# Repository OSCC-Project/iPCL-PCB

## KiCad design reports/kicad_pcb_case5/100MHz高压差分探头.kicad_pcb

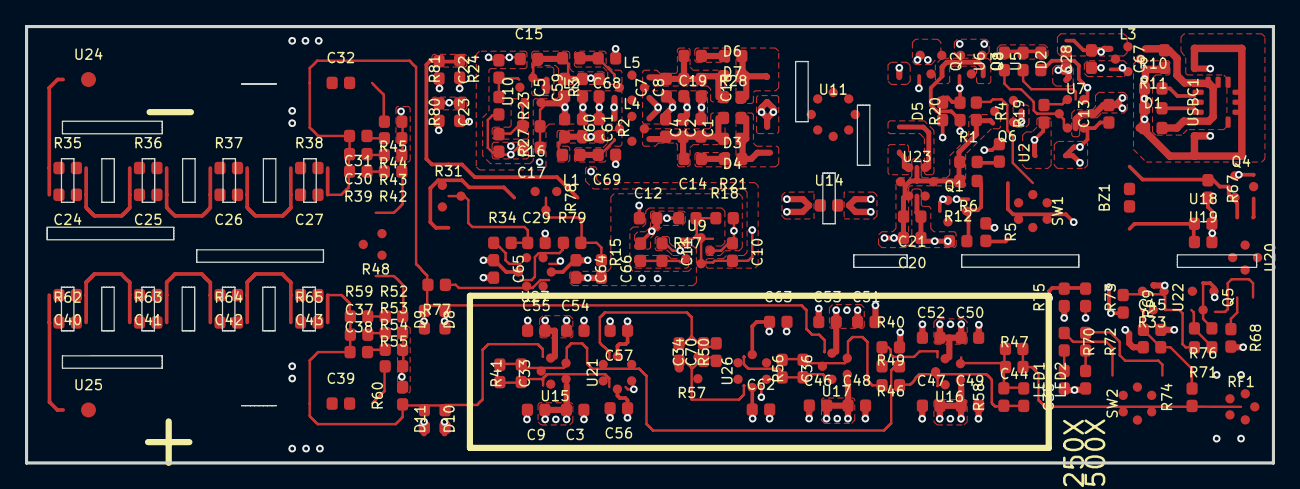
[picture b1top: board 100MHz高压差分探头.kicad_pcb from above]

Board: 4 copper layers, 100.0 x 35.0 mm, 185 parts (0 on the bottom side), 91 nets.

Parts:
BZ1: 3f1529bbaa4c4125a10b70c2df94fc11
C1, C2, C3, C4, C5, C7, C8, C9, C10, C11, C12, C13, C14, C15, C16, C17, C18, C19, C20, C21, C22, C23, C28, C29, C30, C31, C33, C35, C36, C37, C38, C44, C45, C46, C47, C48, C49, C50, C51, C52, C53, C54, C55, C56, C57, C59, C60, C61, C62, C63, C64, C65, C66, C67, C68, C69: 01a79b0e39434d2ea8de62503f4b7cf0
C24, C25, C26, C27, C40, C41, C42, C43: 50b6f6c4261345bcae1f204b32f03376
C32, C39: 0bbfdf4e88d143f6bbe0c44ba3fab90c
C34, C70: b083607f37af4680b9e4592262e65319
D1, D3, D4, D5, D6, D7, D8, D9, D10, D11: 2221e8d1e2a34b8f89d77a5d79f2ca10
D2: 2d40e6deeb29450e9d1a4a76727988d5
L1, L2: f3d986930d2e4bc98811ac8ef379dce3
L3, L4, L5: a09d160eb8b243d5bb85ea6fb6939f0f
LED1: 65745c81ed8e4f3d8e50d31c896d1acd
LED2: 897dac56033e486aafb175e0d8b9fbf8
Q1, Q2, Q3, Q5, Q6: f399c43c22204b4fb713e57500bec75f
Q4: 2af9f62ae7c849819938fc866dd93b51
R1, R2, R3, R4, R5, R6, R10, R11, R12, R15, R17, R18, R19, R20, R21, R23, R24, R27, R28, R33, R34, R39, R40, R41, R42, R43, R44, R45, R46, R47, R49, R52, R53, R54, R55, R56, R58, R59, R60, R67, R68, R69, R70, R71, R72, R73, R74, R75, R76, R77, R79, R80, R81: 345df099f6c344ecb03f6331ff1faf22
R31, R48, R57, R78: 507339a48b6e4fd2b68fda0a46e27918
R35, R36, R37, R38, R62, R63, R64, R65: 50b6f6c4261345bcae1f204b32f03376
R50: b083607f37af4680b9e4592262e65319
RF1: 1ec777233d6c4149af6d04cb8e51bfe0
SW1, SW2: 48ba2fcf414c4ed1a85436e39ba2de45
U2, U6, U8: 7f88689ddd524e799a2641e85c3efaab
U5, U18, U19: 345df099f6c344ecb03f6331ff1faf22
U7, U23: 3b6e914cb86f4d04bf420dafbc51a538
U9: c412defa74a04dd7acaf0683044d5107
U10: 3a5982d0234d420ea4a672c9ef07185e
U11: a63def889ecb4197ab4f0e3660f255c6
U14: 1ff305d16cc04ffa85117006eafe7e4e
U15, U16, U17: 78df07149524430e9275017333e781e3
U20: 9a9a9ba2542742fcbc0be96d8fc2a154
U21, U26, U27: 34bb1eb335204bddbf3cbc7fe83f455e
U22: f399c43c22204b4fb713e57500bec75f
U24, U25: 0ff93004c7c14642a7edf0b7216f2991
USBC1: d71d1ea865754169be761115f6d42a03

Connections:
50X_BIAS_IN: R79.1, U27.3
500X_BIAS_IN: R34.1, U27.1
$1N9: R10.2, USBC1.B5
$1N10: R11.2, USBC1.A5
$1N17: D6.2, D7.2, R28.1, U11.5
$1N18: C14.1, R21.2
$1N19: C19.1, R28.2
$1N29: R19.2, U7.6
$1N31: U6.1, U7.1
$1N32: U7.5, U8.1
$1N34: U5.2, U6.2, U8.2
$1N35: Q2.2, Q3.2, R20.1
$1N37: D3.1, D4.1, R21.1, U11.8
$1N38: Q1.3, U2.1
$1N39: Q1.1, R6.1, R12.2
$1N42: R1.2, U2.2
$1N44: D5.2, Q2.1, Q3.1, R20.2, SW1.2
$1N50: U11.2, U23.4
$1N51: U11.1, U23.6
$1N70: C11.2, R15.1, U9.5
$1N80: C16.2, R27.1, U10.5
$1N84: R17.1, R18.1, U9.4
$1N85: R23.1, R24.1, U10.4
$1N87: R5.2, SW1.3
$1N88: Q6.1, R4.1, SW1.5
$1N8838: C69.2, L1.1, L4.4
$1N8925: C68.2, L2.1, L5.1
$2N9: C35.1, C44.2, R47.1, R58.2, U16.1
$2N10: C36.1, R49.1, R56.2, U17.1
$2N11: C33.1, R41.2, R46.1, U15.1
$2N13: R40.1, R46.2, U16.3
$2N15: C35.2, R49.2, R58.1, U16.4
$2N40: C32.2, R45.2
$2N44: C24.2, R35.1, U24.1
$2N45: C40.2, R62.1, U25.1
$2N46: R52.1, R59.2
$2N47: R48.1, R52.2
$2N48: C40.1, C41.2, R62.2, R63.1
$2N50: C41.1, C42.2, R63.2, R64.1
$2N51: C42.1, C43.2, R64.2, R65.1
$2N55: R42.1, R48.3
$2N56: R39.1, R42.2
$2N57: C26.1, C27.2, R37.2, R38.1
$2N58: C25.1, C26.2, R36.2, R37.1
$2N60: C24.1, C25.2, R35.2, R36.1
$2N70: R73.2, SW2.6
$2N71: R70.1, SW2.1
$2N72: R72.1, SW2.3
$2N74: LED1.2, R70.2
$2N75: LED2.2, R72.2
$2N78: C45.1, R33.2, R74.2, U22.1
$2N83: R69.1, R71.2, U22.2
$2N86: R68.1, U20.1
$2N88: Q5.1, R71.1, R76.2
$2N90: Q4.1, U20.3
$2N92: BZ1.1, U18.1, U19.1
$2N93: BZ1.2, Q4.3, R67.1, U20.4
$2N95: C31.1, R44.2
$2N96: C37.2, R53.1
$2N97: C30.1, R43.2
$2N98: C38.2, R54.1
$2N127: C39.2, R55.1
$2N12584: Q5.2, U20.2
$2N25458: C29.1, R31.2, R34.2
$2N25616: C66.1, R78.2, R79.2
+2.5V: C3.2, C9.1, C12.2, C46.2, C47.2, C48.1, C49.1, C56.1, C62.1, C64.1, D8.2, D10.2, R15.2, R17.2, R80.1, SW2.4, SW2.5, U15.5, U16.5, U17.5, U21.5, U26.5, U27.5
+4.5V: C10.2, C60.2, C61.2, L1.2, R2.2, R68.2, R69.2, SW2.2, U9.1, U9.3
+5V: C20.2, C21.2, D2.1, Q3.3, Q6.2, R1.1, R4.2, R6.2, R67.2, SW1.6, U18.2, U19.2, U23.1, U23.5
+VCC: C1.2, C2.2, C4.1, C14.2, D3.2, D4.2, L4.3
-2.5V: C17.2, C50.1, C51.1, C52.2, C53.2, C54.1, C55.2, C57.1, C63.1, C65.1, D9.1, D11.1, R23.2, R27.2, R75.1, R81.1, U15.2, U16.2, U17.2, U21.2, U26.2, U27.2
-4.5V: C5.2, C15.2, C59.2, L2.2, LED1.1, LED2.1, Q5.3, R3.2, R76.1, U10.2, U10.3
-VCC: C7.2, C8.2, C18.1, C19.2, D6.1, D7.1, L5.2
BAT+: C13.1, Q2.3, U7.3
BAT_CHRG: Q6.3, U5.1, U7.4
BIAS_OUT: R77.1, U27.4
EGND: C67.1, D1.1, L3.3, R10.1, R11.1, USBC1.1, USBC1.2, USBC1.3, USBC1.4, USBC1.A12, USBC1.B12
GND: C3.1, C5.1, C9.2, C10.1, C11.1, C12.1, C15.1, C16.1, C17.1, C22.2, C23.2, C29.2, C45.2, C46.1, C47.1, C48.2, C49.2, C50.2, C51.2, C52.1, C53.1, C54.2, C55.1, C56.2, C57.2, C59.1, C60.1, C61.1, C62.2, C63.2, C64.2, C65.2, C66.2, C68.1, C69.1, L4.1, L5.4, R2.1, R3.1, R18.2, R24.2, R33.1, R40.2, R43.1, R44.1, R45.1, R48.2, R53.2, R54.2, R55.2, R60.2, RF1.1, RF1.2, RF1.3, RF1.4, U9.2, U10.1, U22.3
HV_IN+: C37.1, C38.1, C39.1, C43.1, D10.1, D11.2, R59.1, R60.1, R65.2, U15.3
HV_IN-: C27.1, C30.2, C31.2, C32.1, D8.1, D9.2, R38.2, R39.2, R77.2, U17.3
PGND: C13.2, C20.1, C21.1, C28.1, L3.4, Q1.2, Q4.2, R5.1, R12.1, R19.1, SW1.4, U7.2, U11.4, U14.2, U23.2
POWER_IN: C67.2, D1.2, L3.2, USBC1.A9, USBC1.B9
SET_EN: R73.1, R75.2, U21.6, U26.6, U27.6
SGND: C1.1, C2.1, C4.2, C7.1, C8.1, C18.2, L4.2, L5.3, U11.6, U11.7, U14.1
SIGNAL_A: C33.2, R41.1, U15.4, U21.4
SIGNAL_B: C34.2, C70.2, R50.1, R57.3, U21.3
SIGNAL_C: C34.1, C70.1, R50.2, R57.1, R57.2, U26.4
SIGNAL_D: C36.2, R56.1, U17.4, U26.3
SIGNAL_OUT: C44.1, R47.2, R74.1, RF1.5
VBUS: C28.2, D2.2, D5.1, L3.1
VCC_BIAS: C23.1, R31.3, R78.3, R80.2
VSS_BIAS: C22.1, R31.1, R78.1, R81.2

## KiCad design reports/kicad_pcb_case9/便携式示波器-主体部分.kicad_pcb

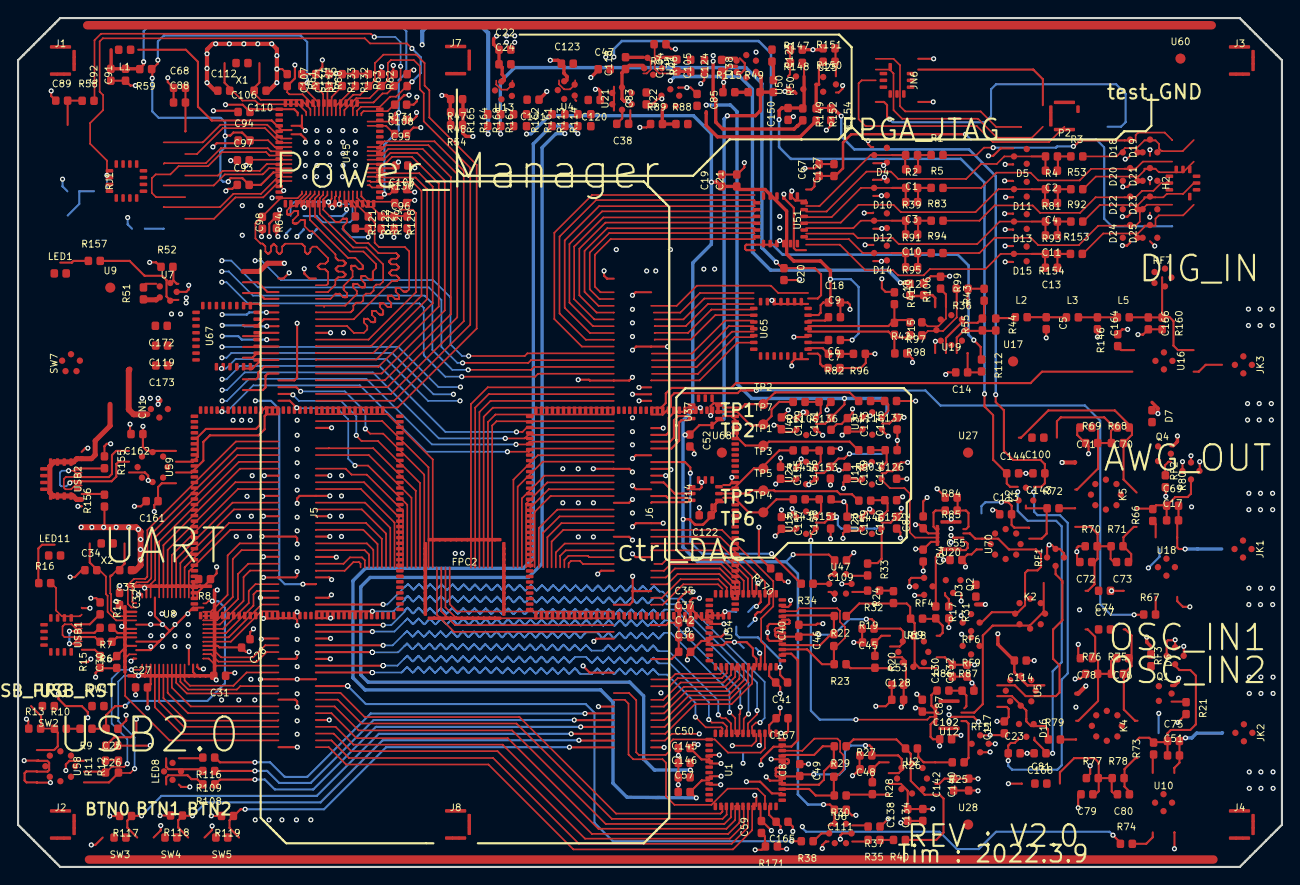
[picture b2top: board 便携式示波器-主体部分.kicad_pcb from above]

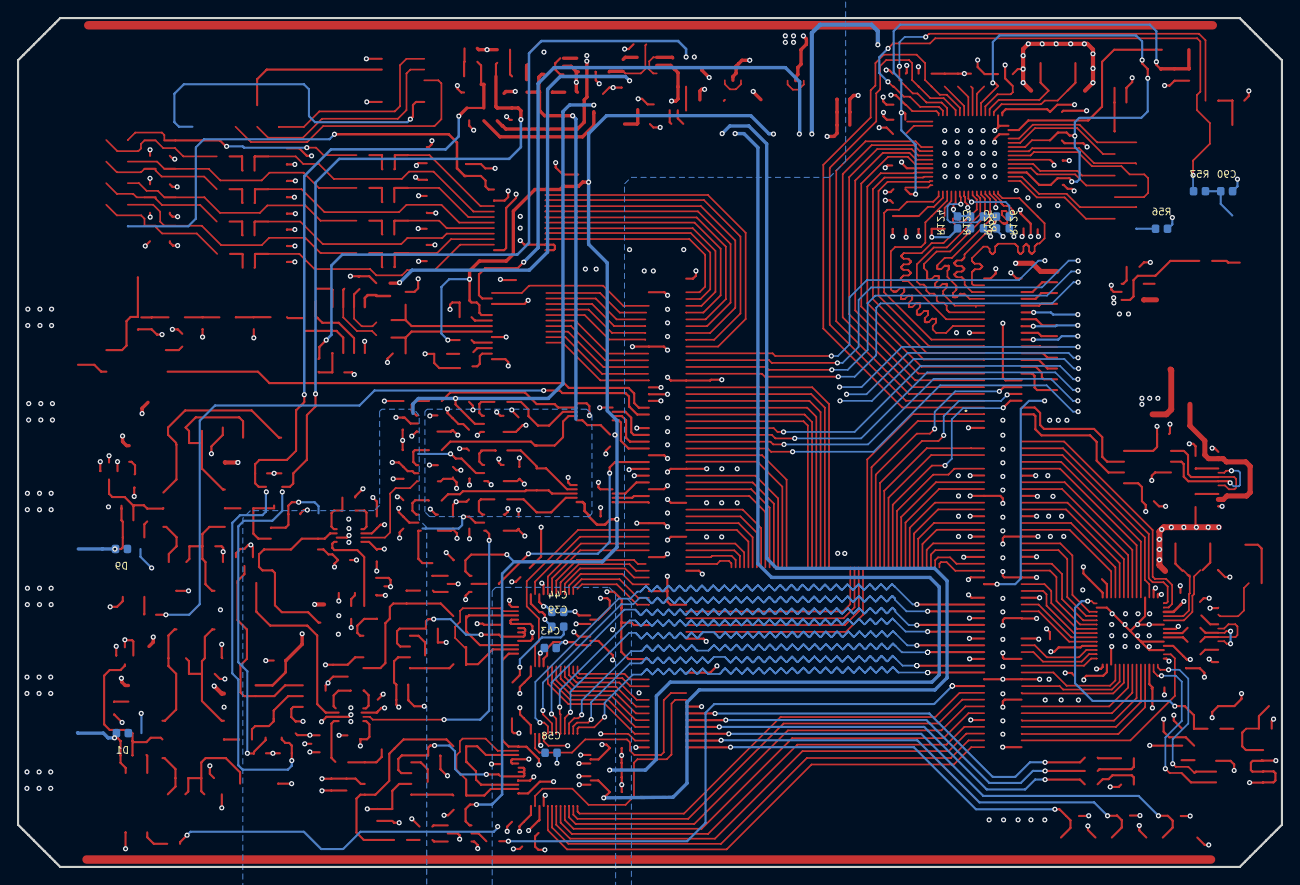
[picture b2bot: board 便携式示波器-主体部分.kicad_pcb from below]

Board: 4 copper layers, 148.8 x 100.0 mm, 424 parts (14 on the bottom side), 396 nets.

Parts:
C1, C2, C3, C4, C5, C6, C7, C8, C9, C10, C11, C12, C13, C14, C16, C17, C18, C19, C20, C21, C22, C23, C24, C25, C26, C27, C28, C30, C31, C32, C35, C36, C37, C38, C39, C40, C41, C42, C43, C44, C45, C47, C48, C50, C51, C52, C53, C55, C57, C58, C59, C67, C68, C69, C75, C82, C83, C84, C85, C87, C88, C89, C90, C91, C92, C93, C94, C95, C96, C97, C98, C102, C103, C104, C105, C106, C107, C108, C109, C111, C113, C114, C117, C118, C120, C121, C122, C123, C124, C126, C127, C128, C129, C130, C131, C132, C133, C134, C135, C136, C137, C138, C139, C140, C141, C142, C143, C144, C145, C146, C150, C151, C152, C153, C154, C155, C156, C157, C158, C159, C160, C161, C162, C164, C165, C166, C167, C168, C171: 07a3b3d25cb24a23b41b29c7c43f76a4
C15, C33, C34, C46, C49, C70, C71, C72, C73, C76, C78, C79, C80, C110, C112, C125: ecf74e3ff335461599c94ce8e76dec14
C74, C77, C81, C100: 6fe1afaffdd746fdafbe654c8791fdbb
C119: e953
C172: e643
C173: e975
CN1: 97ec1ec1f0bd4617b79c42a0c47e9ab8
D1, D9: 5c734f664c17495bb14b7ecc2dc1b01d
D2, D4, D5, D10, D11, D12, D13, D14, D15, D16: 7077287a35204f9fafd72688a0c6c785
D3, D6, D7: a427f604374a450b87681949da315927
D18, D19, D20, D21, D22, D23, D24, D25: ba35f145f3334095baaa2c5d5d7ab9c4
FPC2: acd62fa7532c46e08cf669b9fb3d13ec
H2: e31
J1, J2, J3, J4, J7, J8: 3e270af6f27d4b5baf20436f71ab87c1
J5, J6: 836487c508f5438db19a04d639868192
JK1, JK2, JK3: d6ee2ffcc263406887e9d63c7b0519c9
JN6: 634f5b4bbd774284bf12773d4cedab9f
K2, K4, K5: eac199bb981b499388a4d5b0c93f63eb
L1: cd119f9e95084eb78cad3b7cd4ac4ea6
L2, L3, L5: 5d95bff7b0ab48bfa5dc7e220d271b5c
LED1, LED11: 40f9432dd09647dfa891c462f023b0b0
LED8: e8caabb99a05482f87a41ff9bf5e5609
P2: 8c9b220d407a4bc496bdc03fba551d8c
Q1, Q2, Q4: 3287ea164c0a4816a855ac08f4e68882
R1, R2, R3, R4, R5, R6, R7, R8, R9, R10, R11, R12, R13, R14, R15, R16, R17, R18, R19, R20, R21, R22, R23, R24, R25, R26, R27, R28, R29, R30, R31, R32, R33, R34, R35, R36, R37, R38, R39, R40, R41, R42, R43, R44, R45, R46, R47, R48, R49, R50, R51, R52, R53, R54, R55, R56, R57, R58, R59, R60, R61, R62, R63, R64, R65, R66, R67, R68, R69, R70, R71, R72, R73, R74, R75, R76, R77, R78, R79, R80, R81, R82, R83, R84, R85, R86, R87, R88, R89, R90, R91, R92, R93, R94, R95, R96, R97, R98, R99, R106, R108, R109, R110, R111, R112, R113, R114, R115, R116, R117, R118, R119, R121, R122, R123, R124, R125, R126, R127, R128, R129, R130, R131, R132, R133, R134, R135, R143, R144, R145, R146, R147, R148, R149, R150, R151, R152, R153, R154, R155, R156, R157, R160, R161, R162, R164, R165, R167, R168, R170, R171: 43e5336c61b34dc782468a16d014e54d
RF1: e240
RF2: e2175
RF3: e25
RF4, RF5, RF6, RF9: 4e1d505314b3485a805716e4f50938d0
RF7: e4576
RJ1: 3276e94015d243a8b1987b283792c934
SW1, SW2, SW3, SW4, SW5: 7bb28a98aeac42d1ad801580e2fd9f70
SW7: e199
TP1, TP2, TP3, TP4, TP5, TP7: a4d664abb7a84b85a721b0f8f4caac91
U1, U54: 73b97067b09c48fdada0ea156bb47d30
U2: e231
U3, U11, U15, U23, U24, U38, U40: e9e4340cd3bd4d00a98771ccbc2147d9
U4, U13, U31: a5e6817750744227afed6be8097af0e7
U5, U58, U70: cc666a3ed81142bf901b0a0a8eae77fe
U6, U21, U47: 3046c1046c0c445eaf4abd679cb86288
U7, U22: e6e3948347364938bef4679a6c12bf30
U8: 053d832a12d44255a6c20dd47eb12ddf
U9: e4138
U10, U16, U18: 8c8b562b2c5a4e9f8b0b666146522526
U12, U20: d6e84d3e079e4e6d93029185448293be
U14, U37: 0e9d827b01c2473595ccff7f821a0fa7
U17: e123
U19: 09ce974493c54d8f8ba4eda961c351e3
U25, U50: 3287ea164c0a4816a855ac08f4e68882
U27, U28, U68: 2a0be85b264c426c9105224b5d9be198
U45: e3aaf21cb8f74bf5b3ffddae42e3b778
U51: e09dcdb7932c4e7fbdbbbb8b6cb2ff6e
U59: 44120597447e46d79e3593f8a78a64d1
U60: e2722
U65: e46
U67: e4557
U69: e214
USB1, USB2: b67455ad1fe74fee852a4e157a78bad8
X1, X2: 970fb1cc16ad4744a5ddbbdc55b3fc45

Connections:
1V8_VREF: R49.2, R50.2, U3.4, U11.4, U14.5, U15.4, U23.4, U24.4, U37.5, U38.1, U40.4
$2N3316: R8.2, U8.44
$2N3328: R10.1, R13.2, SW2.2, U58.1
$2N22466: LED11.1, R16.1
$4N2102: R51.2, U7.4
$4N2693: R52.2, U7.3
$4N30038: C38.2, U21.5
$4N30093: C38.1, U21.6
$4N32180: R88.1, R89.2, U22.4
$4N58970: C104.1, R45.2, R46.1, U31.4
$4N102963: R147.1, R148.2, U50.2
$4N105094: R150.1, R151.2, U25.2
$4N131424: C119.1, C172.1, C173.1, CN1.1, R51.1, SW7.2, U7.5
$6N577: C17.2, C69.2, D9.1, JK1.1, U18.3
$6N625: R66.1, U18.4
$6N717: R67.2, U18.1
$6N1817: C70.1, C100.2, K5.7, R68.2
$6N1853: C70.2, C71.1, C100.1, K5.2, R68.1, R69.2
$6N2746: C72.1, C73.2, C74.2, K5.4, R70.2, R71.1
$6N2880: C73.1, K5.5, R71.2
$6N3162: K5.3, R72.2
$6N3340: D2.3, R72.1, U70.3
$6N5199: C76.1, C77.2, K4.7, R75.2
$6N5200: C51.1, C75.1, K4.6, R73.2, RF3.1
$6N5202: C76.2, C77.1, C78.1, K4.2, R75.1, R76.2
$6N5203: C79.1, C80.2, C81.2, K4.4, R77.2, R78.1
$6N5204: C80.1, K4.5, R78.2
$6N5206: K4.3, R79.2
$6N5207: D16.3, R79.1, U5.3
$6N11215: R73.1, U10.4
$6N11216: C51.2, C75.2, D1.1, JK2.1, U10.3
$6N11218: R74.2, U10.1
$6N42224: Q4.1, R80.1
$6N42735: Q1.1, R21.1
$6N46533: C17.1, C69.1, K5.6, R66.2, RF2.1
$9N6643: LED1.1, R157.1
$9N15851: LED8.2, R108.2
$9N15883: LED8.4, R116.2
$9N16326: LED8.3, R109.2
$11N594: R84.1, U20.5
$11N596: R84.2, R85.1, U20.4
$11N600: R86.1, U12.5
$11N602: R86.2, R87.1, U12.4
$11N609: K2.6, RF9.1, U12.3
$11N2263: R17.1, RF4.1, U20.1
$11N2434: R25.1, RF5.1, U12.1
$11N15082: R32.2, U47.1
$11N15190: R33.2, U47.3
$11N21228: R17.2, R18.1, U69.8
$11N21637: R18.2, R22.1, R24.1, U69.5
$11N21987: R20.2, R23.1, U69.4
$11N32769: R28.2, R30.1, U2.4
$11N32770: R25.2, R26.1, U2.8
$11N32771: R26.2, R29.1, R40.1, U2.5
$11N32776: R27.2, R28.1, U2.1
$11N34575: R19.2, R20.1, U69.1
$11N44064: R34.1, U47.5
$11N45056: R35.2, U6.1
$11N45057: R37.2, U6.3
$11N45063: R38.1, U6.5
$11N62502: Q2.1, R31.1
$13N19030: JK3.1, U16.3
$13N22280: C164.1, L3.2, L5.1
$13N50350: R97.1, R99.2, U19.3
$13N50358: R36.2, R98.1, U19.2
$13N50720: R36.1, R43.2, U19.1
$13N50935: C15.1, R41.2, R97.2, U65.22
$13N50945: C15.2, R42.1, R98.2, U65.21
$13N51622: C5.1, L2.2, L3.1
$13N51745: R43.1, R55.2, U19.6
$13N52041: R44.2, R55.1, U19.7
$13N52059: L2.1, R44.1
$13N52787: C6.1, U65.17
$13N53261: R82.2, U65.18
$13N53282: R82.1, R96.2
$13N53522: C7.2, U65.19
$13N53699: C9.1, U65.23
$13N53994: R146.1, U16.1
$13N54030: C166.1, L5.2, R160.1, RF7.5, U16.4
$14N2427: C68.2, C88.2, RJ1.P1
$14N2610: R56.2, RJ1.P10
$14N2784: C89.2, R58.1, RJ1.11
$14N2791: C90.2, R57.1, RJ1.13
$14N17231: R134.1, U45.56
$14N17305: R135.2, U45.58
$14N17416: C110.2, U45.61, X1.1
$14N17453: C112.2, U45.62, X1.2
$15N1230: C136.2, R110.1, U40.3
$15N1237: C137.2, R111.1, U3.3
$15N1251: C126.2, R90.1, U11.3
$15N4262: C151.2, R143.1, U15.3
$15N4269: C152.2, R144.1, U23.3
$15N4283: C153.2, R145.1, U24.3
$15N8686: C125.2, R50.1
$15N15216: R49.1, R115.2
$16N832: C1.1, R1.1, R2.1
$16N1245: C2.1, R3.1, R4.1
$16N1889: C3.1, R5.1, R39.1
$16N2210: C4.1, R53.1, R81.1
$16N3886: C10.1, R83.1, R91.1
$16N3891: C11.1, R92.1, R93.1
$16N3896: C12.1, R94.1, R95.1
$16N3901: C13.1, R153.1, R154.1
+VA: C53.2, C55.2, C84.1, C102.1, C104.2, C105.2, C114.2, C124.2, C128.2, C129.2, C133.2, C134.2, C138.2, C139.2, C155.2, C157.2, C159.2, D3.1, D6.1, D7.1, K2.1, K4.1, K5.1, R46.2, R146.2, R149.2, U2.3, U3.6, U5.7, U11.6, U12.8, U15.6, U20.8, U23.6, U24.6, U31.5, U38.4, U38.6, U40.6, U69.3, U70.7
-VA: C82.1, C85.2, C87.2, C113.2, C117.2, C130.2, C131.2, C132.2, C135.2, C140.2, C141.2, C142.2, C156.2, C158.2, C160.2, R88.2, R152.2, U2.6, U3.2, U5.4, U11.2, U12.6, U15.2, U20.6, U22.5, U23.2, U24.2, U40.2, U69.6, U70.4
ADC1_CLKA: J6.75, U54.47
ADC1_CLKB: J6.77, U54.14
ADC1_D0A: J6.119, U54.37
ADC1_D0B: J6.97, U54.24
ADC1_D1A: J6.121, U54.38
ADC1_D1B: J6.95, U54.23
ADC1_D2A: J6.125, U54.39
ADC1_D2B: J6.91, U54.22
ADC1_D3A: J6.127, U54.40
ADC1_D3B: J6.89, U54.21
ADC1_D4A: J6.129, U54.41
ADC1_D4B: J6.87, U54.20
ADC1_D5A: J6.131, U54.42
ADC1_D5B: J6.85, U54.19
ADC1_D6A: J6.133, U54.43
ADC1_D6B: J6.81, U54.18
ADC1_D7A: J6.135, U54.44
ADC1_D7B: J6.79, U54.17
ADC1_IN: C46.1, R23.2, U54.2, U54.11
ADC1_IN_N: C46.2, R22.2, U54.3, U54.10
ADC1_VERF: C40.1, C45.1, U54.5, U54.6, U54.7, U69.2
ADC2_CLKA: J6.126, U1.47
ADC2_CLKB: J6.124, U1.14
ADC2_D0A: J5.123, U1.37
ADC2_D0B: J5.117, U1.24
ADC2_D1A: J5.125, U1.38
ADC2_D1B: J5.115, U1.23
ADC2_D2A: J5.127, U1.39
ADC2_D2B: J5.111, U1.22
ADC2_D3A: J5.129, U1.40
ADC2_D3B: J5.109, U1.21
ADC2_D4A: J5.133, U1.41
ADC2_D4B: J5.105, U1.20
ADC2_D5A: J5.135, U1.42
ADC2_D5B: J5.103, U1.19
ADC2_D6A: J5.137, U1.43
ADC2_D6B: J5.99, U1.18
ADC2_D7A: J5.139, U1.44
ADC2_D7B: J5.97, U1.17
ADC2_IN: C49.1, R30.2, U1.2, U1.11
ADC2_IN_N: C49.2, R29.2, U1.3, U1.10
ADC2_VREF: C8.1, C48.1, U1.5, U1.6, U1.7, U2.2
AGND: C5.2, C6.2, C9.2, C14.2, C16.2, C18.2, C19.2, C20.2, C21.2, C22.1, C23.2, C24.1, C39.1, C40.2, C41.1, C45.2, C47.1, C48.2, C53.1, C55.1, C67.2, C71.2, C72.2, C74.1, C78.2, C79.2, C81.1, C82.2, C83.1, C84.2, C85.1, C87.1, C102.2, C105.1, C109.1, C111.1, C113.1, C114.1, C117.1, C118.1, C120.1, C123.1, C124.1, C125.1, C126.1, C127.2, C128.1, C129.1, C130.1, C131.1, C132.1, C133.1, C134.1, C135.1, C136.1, C137.1, C138.1, C139.1, C140.1, C141.1, C142.1, C143.2, C144.2, C150.1, C151.1, C152.1, C153.1, C154.2, C155.1, C156.1, C157.1, C158.1, C159.1, C160.1, C164.2, C165.1, C166.2, C167.1, C168.2, C171.1, D1.2, D4.1, D5.1, D9.2, D10.1, D11.1, D12.1, D13.1, D14.1, D15.1, D18.3, D19.3, D20.3, D21.3, D22.3, D23.3, D24.3, D25.3, H2.2, JK1.2, JK2.2, JK3.2, JN6.2, JN6.10, P2.2, P2.10, Q1.2, Q2.2, Q4.2, R19.1, R27.1, R41.1, R42.2, R45.1, R47.1, R48.1, R54.1, R69.1, R70.1, R76.1, R77.1, R85.2, R87.2, R89.1, R96.1, R99.1, R115.1, R148.1, R150.2, R160.2, R170.1, R171.1, RF1.2, RF1.3, RF1.4, RF2.2, RF2.3, RF2.4, RF3.2, RF3.3, RF3.4, RF4.2, RF4.3, RF4.4, RF5.2, RF5.3, RF5.4, RF6.2, RF6.3, RF6.4, RF7.1, RF7.2, RF7.3, RF7.4, RF9.2, RF9.3, RF9.4, U4.2, U6.2, U6.6, U10.2, U12.0, U12.2, U13.2, U17.1, U18.2, U19.5, U20.0, U20.2, U21.2, U22.1, U25.1, U31.2, U38.2, U38.3, U38.5, U47.2, U47.6, U50.3, U60.1, U65.16, U65.20
AN_GO: R121.1, U45.29
AVCC1V0: C93.2, C94.2, C121.2, R59.1, U45.7, U45.13, U45.59
AVCC3V0: C37.2, C39.2, C41.2, C42.2, C145.2, C146.2, C165.2, C167.2, R161.1, R162.1, U1.13, U1.30, U1.31, U1.48, U54.13, U54.30, U54.31, U54.48
AVCC3V3: C7.1, C18.1, C19.1, C21.1, C52.1, C109.2, C111.2, C122.1, D4.2, D5.2, D10.2, D11.2, D12.2, D13.2, D14.2, D15.2, R167.1, R168.1, U6.4, U14.1, U37.1, U47.4, U51.1, U65.24
AVCC5V0: C14.1, R112.2, U19.8
AVEE5V0: C16.1, R106.2, U19.4
AWG2_PROTECT: J6.39, U16.2
A_D0: C1.2, D4.3, R2.2, U51.21
A_D1: C2.2, D5.3, R4.2, U51.20
A_D2: C3.2, D10.3, R39.2, U51.19
A_D3: C4.2, D11.3, R81.2, U51.18
A_D4: C10.2, D12.3, R91.2, U51.17
A_D5: C11.2, D13.3, R93.2, U51.16
A_D6: C12.2, D14.3, R95.2, U51.15
A_D7: C13.2, D15.3, R154.2, U51.14
BTN0: J6.136, R117.1, SW3.1
BTN1: J6.138, R118.1, SW4.1
BTN2: J6.140, R119.1, SW5.1
BTN_DONE: FPC2.50, J6.86
BTN_LEFT: FPC2.49, J6.84
BTN_RIGHT: FPC2.47, J6.80
BTN_SURE: FPC2.48, J6.82
BTN_UP: FPC2.46, J6.76
CC1: R14.2, USB1.A5
CC2: R15.2, USB1.B5
CH1_ATTENUATOR: J6.57, R80.2
CH1_DC: J6.41, R67.1
CH1_GAIN: U11.1, U20.7
CH1_GAIN_ADJ: R90.2, TP1.1, U37.2
CH1_GAIN_BTN: FPC2.42, J6.66
CH1_OFFSET_ADJ: R110.2, TP7.1, U37.3
CH1_OFFSET_BTN: FPC2.43, J6.70
CH1_TRIG: R24.2, R32.1
CH1_TRIG_ADJ: R144.2, TP5.1, U14.3
CH1_TRIG_LEVEL: R33.1, U23.1
CH1_TRIG_OUT: J6.55, R34.2
CH1_VGA: K2.7, RF6.1, U20.3, U70.2, U70.6
CH2_ATTENUATOR: J6.59, R21.2
CH2_DC: J6.137, R74.1
CH2_GAIN: U12.7, U15.1
CH2_GAIN_ADJ: R143.2, TP4.1, U14.2
CH2_GAIN_BTN: FPC2.40, J6.62
CH2_OFFSET_ADJ: R145.2, TP3.1, U14.4
CH2_OFFSET_BTN: FPC2.41, J6.64
CH2_TRIG: R35.1, R40.2
CH2_TRIG_ADJ: R111.2, TP2.1, U37.4
CH2_TRIG_LEVEL: R37.1, U3.1
CH2_TRIG_OUT: J5.121, R38.2
CH2_VGA: K2.5, RF1.1, U5.2, U5.6
CHANNEL_CTRL: J6.45, R31.2
CLKOUT: J5.54, U8.54
D0: D18.1, D18.2, H2.9, R1.2
D1: D19.1, D19.2, H2.10, R3.2
D2: D20.1, D20.2, H2.7, R5.2
D3: D21.1, D21.2, H2.8, R53.2
D4: D22.1, D22.2, H2.5, R83.2
D5: D23.1, D23.2, H2.6, R92.2
D6: D24.1, D24.2, H2.3, R94.2
D7: D25.1, D25.2, H2.4, R153.2
DAC0_DIN: J6.47, U37.8
DAC0_SCLK: J6.49, U37.9
DAC0_SYNC_N: J6.51, U37.10
DAC1_DIN: J6.61, U14.8
DAC1_SCLK: J6.65, U14.9
DAC1_SYNC_N: J6.67, U14.10
DAC2_CLK: J6.9, U65.28
DAC2_D0: J6.31, U65.10
DAC2_D1: J6.29, U65.9
DAC2_D2: J6.27, U65.8
DAC2_D3: J6.25, U65.7
DAC2_D4: J6.23, U65.6
DAC2_D5: J6.19, U65.5
DAC2_D6: J6.17, U65.4
DAC2_D7: J6.15, U65.3
DAC2_D8: J6.13, U65.2
DAC2_D9: J6.11, U65.1
DATA0: J6.20, U51.3
DATA1: J6.18, U51.4
DATA2: J6.16, U51.5
DATA3: J6.14, U51.6
DATA4: J6.12, U51.7
DATA5: J6.10, U51.8
DATA6: J6.8, U51.9
DATA7: J6.6, U51.10
DVCC1V0: C91.2, C92.2, C95.2, C96.2, L1.2, R59.2, U45.33, U45.48
DVCC3V0: C35.2, C36.2, C43.2, C44.2, C50.2, C57.2, C58.2, C59.2, R113.1, R114.1, U1.4, U1.8, U1.9, U1.15, U1.28, U1.33, U1.46, U54.4, U54.8, U54.9, U54.15, U54.28, U54.33, U54.46
DVCC3V3: C20.1, C26.2, C27.2, C28.2, C30.2, C31.2, C32.2, C97.2, C98.2, C103.2, C106.2, C107.2, C108.2, C161.1, C162.1, LED8.1, R8.1, R9.2, R10.2, R11.2, R12.2, R60.2, R61.2, R62.2, R65.2, R117.2, R118.2, R119.2, R121.2, R122.2, R123.2, R124.2, R128.2, R130.2, R132.2, R133.2, R134.2, R164.1, R165.1, RJ1.14, U8.3, U8.7, U8.11, U8.17, U8.27, U8.32, U8.43, U8.55, U45.10, U45.20, U45.26, U45.37, U45.49, U45.60, U45.64, U58.8, U59.5, U59.8, U65.27
ENSWREG: R61.1, U45.57
E_COL: R127.2, R128.1, R129.1, U45.31
E_CRS: J5.19, R130.1, U45.32
E_GTXC: J5.21, U45.34
E_MDC: J5.37, R132.1, U45.53
E_MDIO: J5.39, R133.1, U45.54
E_RESET: J5.27, U45.38
E_RXC: J5.13, U45.24
E_RXD0: J5.5, U45.19
E_RXD1: J5.7, U45.21
E_RXD2: J5.9, U45.22
E_RXD3: J5.11, U45.23
E_RXDV: J5.3, R64.1, U45.18
E_RXER: J5.15, R122.1, U45.30
E_TXC: J5.35, U45.42
E_TXD0: J5.25, U45.36
E_TXD1: J5.29, U45.39
E_TXD2: J5.31, U45.40
E_TXD3: J5.33, U45.41
E_TXEN: J5.23, U45.35
E_TXER: R131.1, U45.47
GND: C8.2, C25.1, C26.1, C27.1, C28.1, C30.1, C31.1, C32.1, C33.1, C34.1, C35.1, C36.1, C37.1, C42.1, C43.1, C44.1, C50.1, C52.2, C57.1, C58.1, C59.1, C68.1, C88.1, C89.1, C90.1, C91.1, C92.1, C93.1, C94.1, C95.1, C96.1, C97.1, C98.1, C103.1, C106.1, C107.1, C108.1, C110.1, C112.1, C119.2, C121.1, C122.2, C145.1, C146.1, C161.2, C162.2, C172.2, C173.2, CN1.2, FPC2.23, FPC2.24, FPC2.25, FPC2.26, J5.2, J5.17, J5.32, J5.45, J5.59, J5.60, J5.65, J5.66, J5.71, J5.72, J5.77, J5.78, J5.83, J5.84, J5.89, J5.90, J5.95, J5.96, J5.101, J5.102, J5.107, J5.108, J5.113, J5.114, J5.119, J5.120, J5.126, J5.131, J5.140, J6.2, J6.5, J6.21, J6.32, J6.53, J6.58, J6.63, J6.68, J6.73, J6.78, J6.83, J6.88, J6.93, J6.98, J6.103, J6.108, J6.113, J6.118, J6.123, J6.128, J6.139, LED1.2, LED11.2, R13.1, R14.1, R15.1, R47.2, R48.2, R52.1, R54.2, R56.1, R63.2, R64.2, R125.1, R126.1, R127.1, R129.2, R131.2, R135.1, R155.1, R156.1, R170.2, R171.2, RJ1.12, SW1.1, SW2.1, SW3.2, SW4.2, SW5.2, U1.1, U1.12, U1.16, U1.27, U1.29, U1.32, U1.34, U1.45, U7.2, U8.6, U8.10, U8.12, U8.14, U8.26, U8.28, U8.41, U8.53, U8.56, U8.57, U14.7, U37.7, U45.2, U45.4, U45.63, U45.65, U51.11, U51.12, U51.13, U51.22, U54.1, U54.12, U54.16, U54.27, U54.29, U54.32, U54.34, U54.45, U58.2, U58.3, U58.4, U58.7, U59.3, U65.26, U67.1, U67.27, USB1.1, USB1.A1B12, USB1.B1A12, USB2.1, USB2.A1B12, USB2.B1A12
IDC_IO0: J6.26, U67.30
IDC_IO1: J6.28, U67.28
IDC_IO2: J6.30, U67.26
IDC_IO3: J5.12, U67.20
IDC_IO4: J5.16, U67.18
IDC_IO5: J5.20, U67.16
IDC_IO6: J6.33, U67.14
IDC_IO7: J6.35, U67.12
IDC_IO8: J6.37, U67.10
IDC_IO9: J6.46, U67.8
IDC_IO10: J6.48, U67.6
IDC_IO11: J6.50, U67.4
IDC_IO12: J6.52, U67.2
IDC_IO13: J6.24, U67.29
IDC_IO14: J5.6, U67.25
IDC_IO15: J5.8, U67.23
IDC_IO16: J5.10, U67.21
IDC_IO17: J5.14, U67.17
IDC_IO18: J5.18, U67.15
IDC_IO19: J5.22, U67.13
IDC_IO20: J5.24, U67.11
IDC_IO21: J5.26, U67.9
IDC_IO22: J5.28, U67.7
IDC_IO23: J5.30, U67.5
IDC_IO24: J5.91, U67.3
IO1: FPC2.1, J5.87
IO2: FPC2.2, J5.85
IO3: FPC2.3, J5.81
IO4: FPC2.4, J5.79
IO5: FPC2.5, J5.75
IO6: FPC2.6, J5.73
IO7: FPC2.7, J5.69
IO8: FPC2.8, J5.67
IO9: FPC2.9, J5.63
IO10: FPC2.10, J5.61
IO11: FPC2.11, J5.57
IO12: FPC2.12, J5.38
IO13: FPC2.13, J5.53
IO14: FPC2.14, J5.51
IO15: FPC2.15, J5.36
IO16: FPC2.16, J5.34
IO17: FPC2.17, J5.43
IO18: FPC2.18, J5.41
IO19: FPC2.19, J6.106
IO20: FPC2.20, J6.104
IO21: FPC2.21, J6.102
IO22: FPC2.22, J6.100
IO27: FPC2.27, J6.34
IO28: FPC2.28, J6.36
IO29: FPC2.29, J6.38
IO30: FPC2.30, J6.40
IO31: FPC2.31, J6.42
IO32: FPC2.32, J6.44
JTAG_TCK: JN6.1, P2.1
JTAG_TDI: JN6.9, P2.9
JTAG_TDO: JN6.3, P2.3
JTAG_TMS: JN6.5, P2.5
JTAG_VCC: JN6.4, P2.4
LED_B: J6.130, R116.1
LED_G: J6.132, R109.1
LED_R: J6.134, R108.1
LOGIC_DIR: J6.22, U51.2
OSC_FREQ_BTN: FPC2.44, J6.72
OSC_TIME_BTN: FPC2.45, J6.74
PHY_AD0/LED0: R57.2, R62.1, U45.50
PHY_AD1/LED1: R58.2, R63.1, U45.51
PHY_MDI0_N: RJ1.P3, U45.6
PHY_MDI0_P: RJ1.P2, U45.5
PHY_MDI1_N: RJ1.P7, U45.9
PHY_MDI1_P: RJ1.P4, U45.8
PHY_MDI2_N: RJ1.P6, U45.12
PHY_MDI2_P: RJ1.P5, U45.11
PHY_MDI3_N: RJ1.P9, U45.15
PHY_MDI3_P: RJ1.P8, U45.14
PME: R60.1, U45.55
RE1: D7.2, K5.8, Q4.3
RE2: D6.2, K4.8, Q1.3
RE3: D3.2, K2.8, Q2.3
REGOUT: L1.1, U45.3
RXDLY: R124.1, R125.2, U45.28
SELRGV: R65.1, U45.25
SWG_AMP_BTN: FPC2.39, J6.60
SWG_FREQ_BTN: FPC2.38, J6.56
SWG_WAVE_BTN: FPC2.37, J6.54
TXDLY: R123.1, R126.2, U45.27
UART_CC1: R155.2, USB2.A5
UART_CC2: R156.2, USB2.B5
UART_RXD: J5.40, U59.7
UART_TXD: J5.42, U59.6
UART_VCC: SW7.1, USB2.A4B9, USB2.B4A9
USB1_N: U59.2, USB2.A7, USB2.B7
USB1_P: U59.1, USB2.A6, USB2.B6
USB2.0_VCC: R16.2, USB1.A4B9
USB_DM: R6.1, U8.9
USB_DP: R7.1, U8.8
USB_FD0: J5.136, U8.18
USB_FD1: J5.134, U8.19
USB_FD2: J5.132, U8.20
USB_FD3: J5.130, U8.21
USB_FD4: J5.128, U8.22
USB_FD5: J5.124, U8.23
USB_FD6: J5.122, U8.24
USB_FD7: J5.118, U8.25
USB_FD8: J5.76, U8.45
USB_FD9: J5.74, U8.46
USB_FD10: J5.70, U8.47
USB_FD11: J5.68, U8.48
USB_FD12: J5.64, U8.49
USB_FD13: J5.62, U8.50
USB_FD14: J5.58, U8.51
USB_FD15: J5.56, U8.52
USB_FIFOADR0: J5.88, U8.37
USB_FIFOADR1: J5.86, U8.38
USB_FLAGA: J5.116, U8.29
USB_FLAGB: J5.112, U8.30
USB_FLAGC: J5.110, U8.31
USB_IFCLK: J5.138, U8.13
USB_M: R6.2, USB1.A7, USB1.B7
USB_P: R7.2, USB1.A6, USB1.B6
USB_PA0: J5.100, U8.33
USB_PA1: J5.98, U8.34
USB_PA3: J5.92, U8.36
USB_PA6: J5.82, U8.39
USB_PA7: J5.80, U8.40
USB_RESET: C25.2, R9.1, SW1.2, U8.42
USB_SCL: R11.1, U8.15, U58.6
USB_SDA: R12.1, U8.16, U58.5
USB_SLOE: J5.94, U8.35
USB_SLRD: J5.52, U8.1
USB_SLWR: J5.50, U8.2
USB_XIN: C34.2, U8.5, X2.2
USB_XOUT: C33.2, U8.4, X2.1
VCC2V88: C144.1, C150.2, C168.1, D2.2, D16.2, R147.2, R149.1, U50.1
VCC3V0: C120.2, R113.2, R114.2, R161.2, R162.2, U4.5
VCC3V3: C171.2, R164.2, R165.2, R167.2, R168.2, U13.5
VCC5V0: C22.2, C24.2, C47.2, C118.2, C123.2, J6.3, J6.4, R112.1, R157.2, U4.1, U4.3, U7.1, U13.1, U13.3, U21.3, U21.4, U31.1, U31.3, U67.22, U67.24
VCC_DIG: C67.1, C127.1, H2.1, U51.23, U51.24
VEE2V88: C23.1, C143.1, C154.1, D2.1, D16.1, R151.1, R152.1, U25.3
VEE5V0: C83.2, R106.1, U21.1, U22.2, U22.3
